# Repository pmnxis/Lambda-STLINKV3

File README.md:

Lambda-STLINKv3
=========================

### Alternative PCB for cheap use of STLINK-V3

#### PCB Routing for public usage version is WIP. Please Wait

Front Side | Back Side
---|:---:|
|
_This PCB design is part of Inc.GPARK's works. But it's being open for public usage._

Lambda-STLINKv3 uses legit STLINK-V3 MINI from STMicroelectronics.

This PCB may suitable when deploy lots of STLINK in project members or any purpose but wanna decrease prices for buy STLINK-V3.

BOM
-------------------------

Total Price /wo POGO Cable : aprx 12.5 USD

Total Price /w  POGO Cable : aprx 51.5 USD

Standalone STLINK-V3SET : 35.0 USD

Designator | Parts name | Alter Avail | Qty | Prices 
---:|---:|---:|---:|---:|
U1 | STLINK-V3MINI | No | 1 | 10.16$
J1 | 61202021721 | Yes | 1 | 0.90$
J2 | 61201021721 | Yes | 1 | 0.65$
J3 | 61300211121 | Yes | 1 | 0.10$
J4 | 61300311021 | Yes | 1 | 0.30$
Jumper | M7582-05 | Yes | 1 | 0.10$
Extra Cable | TC2050-IDC | ? | 1 | 39.00$

_TC2050-IDC is extra for pogo-pin usage_ 

Make your own custom way
-------------------------

[DM0055046.pdf](https://www.st.com/resource/en/user_manual/dm00555046-stlinkv3mods-and-stlinkv3mini-mini-debuggersprogrammers-for-stm32-stmicroelectronics.pdf)

Lambd-STLINKV3 is following STMicroelectronics' suggest. So you create own breakout board for STM32-JTAG/SWD.

License
-------------------------
MIT License

Jinwoo Park - pmnxis@gmail.com

Inc. GPARK  - dev@gpark.biz

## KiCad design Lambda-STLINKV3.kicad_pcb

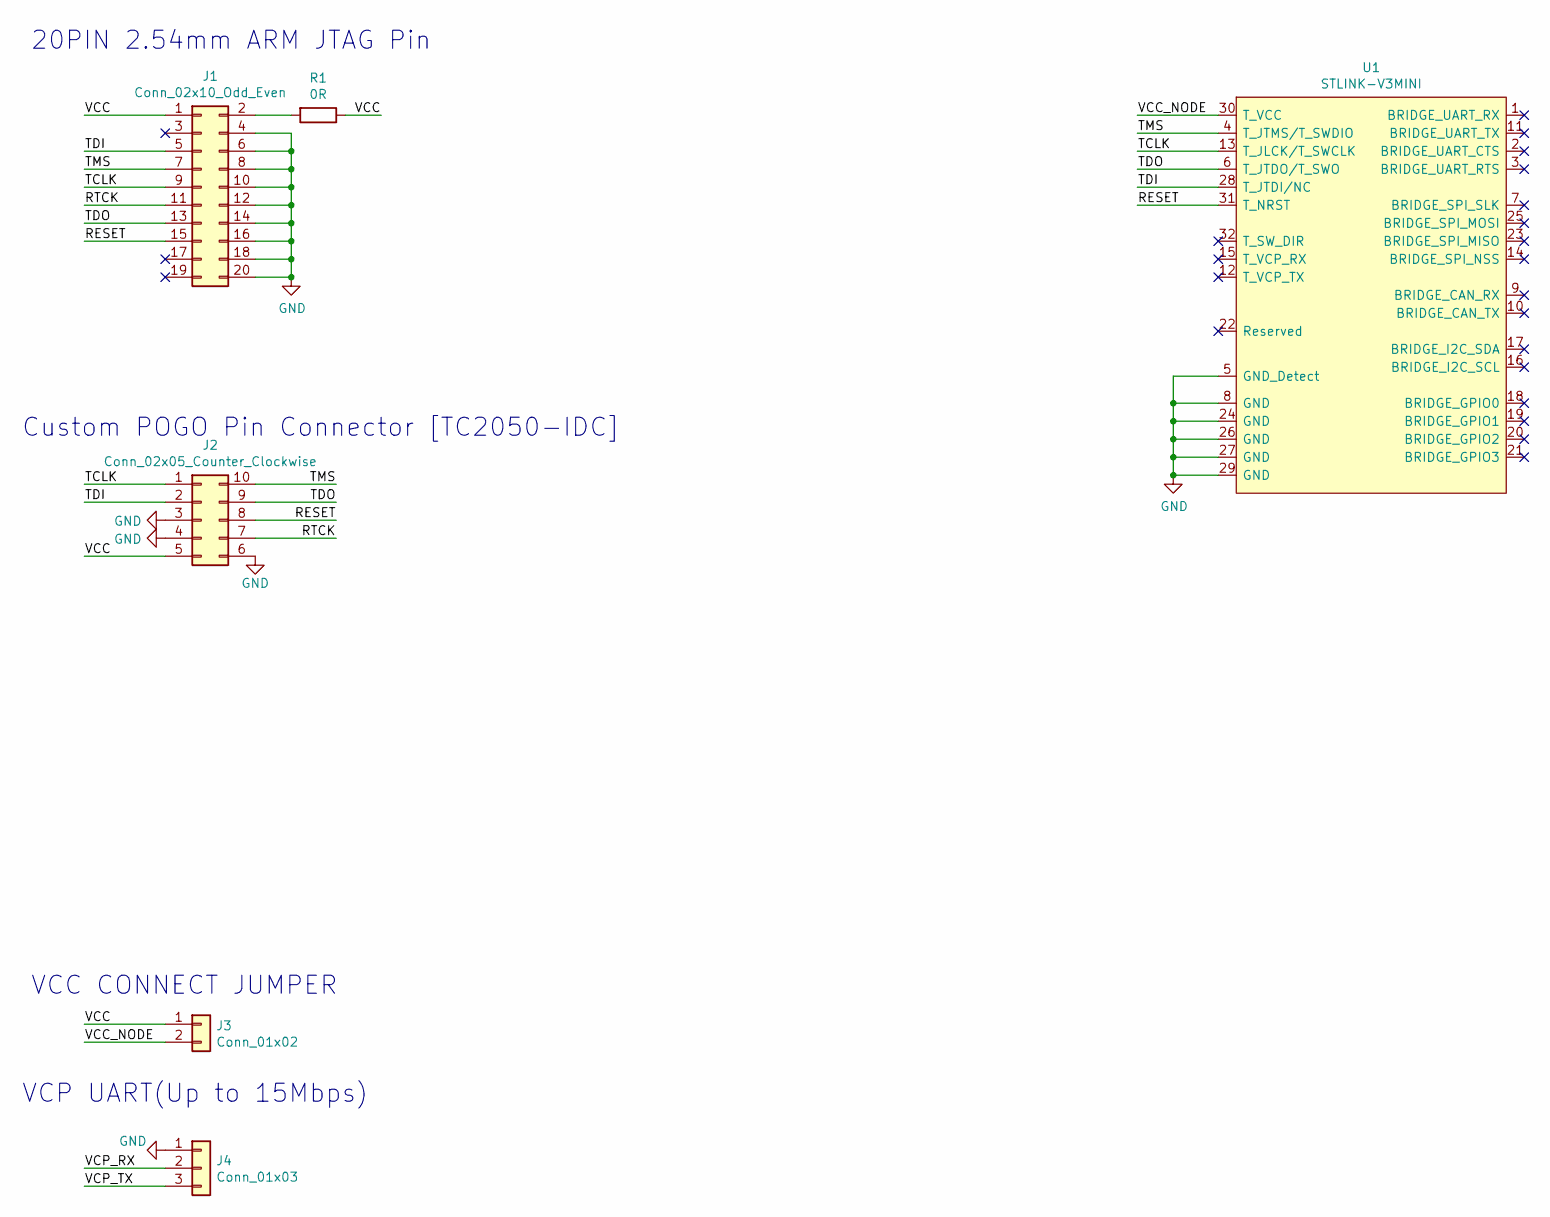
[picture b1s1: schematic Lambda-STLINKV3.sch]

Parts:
J1: Conn_02x10_Odd_Even; IDC-Header_2x10_P2.54mm_Horizontal
J2: Conn_02x05_Counter_Clockwise; IDC-Header_2x05_P2.54mm_Horizontal
J3: Conn_01x02; PinHeader_1x02_P2.54mm_Vertical
J4: Conn_01x03; PinHeader_1x03_P2.54mm_Horizontal
R1: 0R; R_0805_2012Metric
U1: STLINK-V3MINI

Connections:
/RESET: J1.15, J2.8, U1.31 (T_NRST)
/RTCK: J1.11, J2.7
/TCLK: J1.9, J2.1, U1.13 (T_JLCK/T_SWCLK)
/TDI: J1.5, J2.2, U1.28 (T_JTDI/NC)
/TDO: J1.13, J2.9, U1.6 (T_JTDO/T_SWO)
/TMS: J1.7, J2.10, U1.4 (T_JTMS/T_SWDIO)
/VCC: J1.1, J2.5, J3.1, R1.1
/VCC_NODE: J3.2, U1.30 (T_VCC)
/VCP_RX: J4.2
/VCP_TX: J4.3
GND: J1.4, J1.6, J1.8, J1.10, J1.12, J1.14, J1.16, J1.18, J1.20, J2.3, J2.4, J2.6, J4.1, U1.5 (GND_Detect), U1.8 (GND), U1.24 (GND), U1.26 (GND), U1.27 (GND), U1.29 (GND)
unnamed: J1.2, R1.2

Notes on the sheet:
20PIN 2.54mm ARM JTAG Pin
VCC CONNECT JUMPER
Custom POGO Pin Connector [TC2050-IDC]
VCP UART(Up to 15Mbps)

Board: 2 copper layers, 6 parts (1 on the bottom side), 10 nets, no tracks yet.

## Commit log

2020-11-08 First Update.
    Currently PCB routing is yet. it will be upload soon. Thanks.
